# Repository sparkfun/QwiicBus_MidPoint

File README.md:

SparkFun QwiicBus MidPoint
========================================

[*SparkFun QwiicBus MidPoint (COM-18000)*](https://www.sparkfun.com/products/18000)

The SparkFun QwiicBus MidPoint works in tandem with the [SparkFun QwiicBus EndPoint](https://www.sparkfun.com/products/16988) to drop in I<sup>2</sup>C connections into a long-distance wired differential I<sup>2</sup>C bus. 
Featuring the PCA9615, the MidPoint translates a standard two-wire I<sup>2</sup>C signal to a 4-wire differential signal to allow long-distance and/or isolated wired buses. The board also includes a buck regulator that can be enabled to combat voltage drop over long distances as well as deliver more current to attached devices.

Repository Contents
-------------------

* **/Hardware** - Eagle design files (.brd, .sch)
* **/Production** - Production panel files (.brd)

Documentation
--------------
* **[Hookup Guide](https://learn.sparkfun.com/tutorials/sparkfun-qwiicbus-hookup-guide)** - Basic hookup guide for the SparkFun QwiicBus (MidPoint and EndPoint).

Product Versions
----------------
* [COM-18000](https://www.sparkfun.com/products/18000)- Initial QwiicBus MidPoint release
* [COM-16988](https://www.sparkfun.com/products/16988) - QwiicBus EndPoint initial release
* [KIT-17250](https://www.sparkfun.com/products/17250) - The SparkFun QwiicBus Kit includes 2 EndPoints, 1 MidPoint and a pair of Ethernet cables to get started with the QwiicBus.

License Information
-------------------

This product is _**open source**_! 

Please review the LICENSE.md file for license information. 

If you have any questions or concerns on licensing, please contact technical support on our [SparkFun forums](https://forum.sparkfun.com/viewforum.php?f=152).

Distributed as-is; no warranty is given.

- Your friends at SparkFun.

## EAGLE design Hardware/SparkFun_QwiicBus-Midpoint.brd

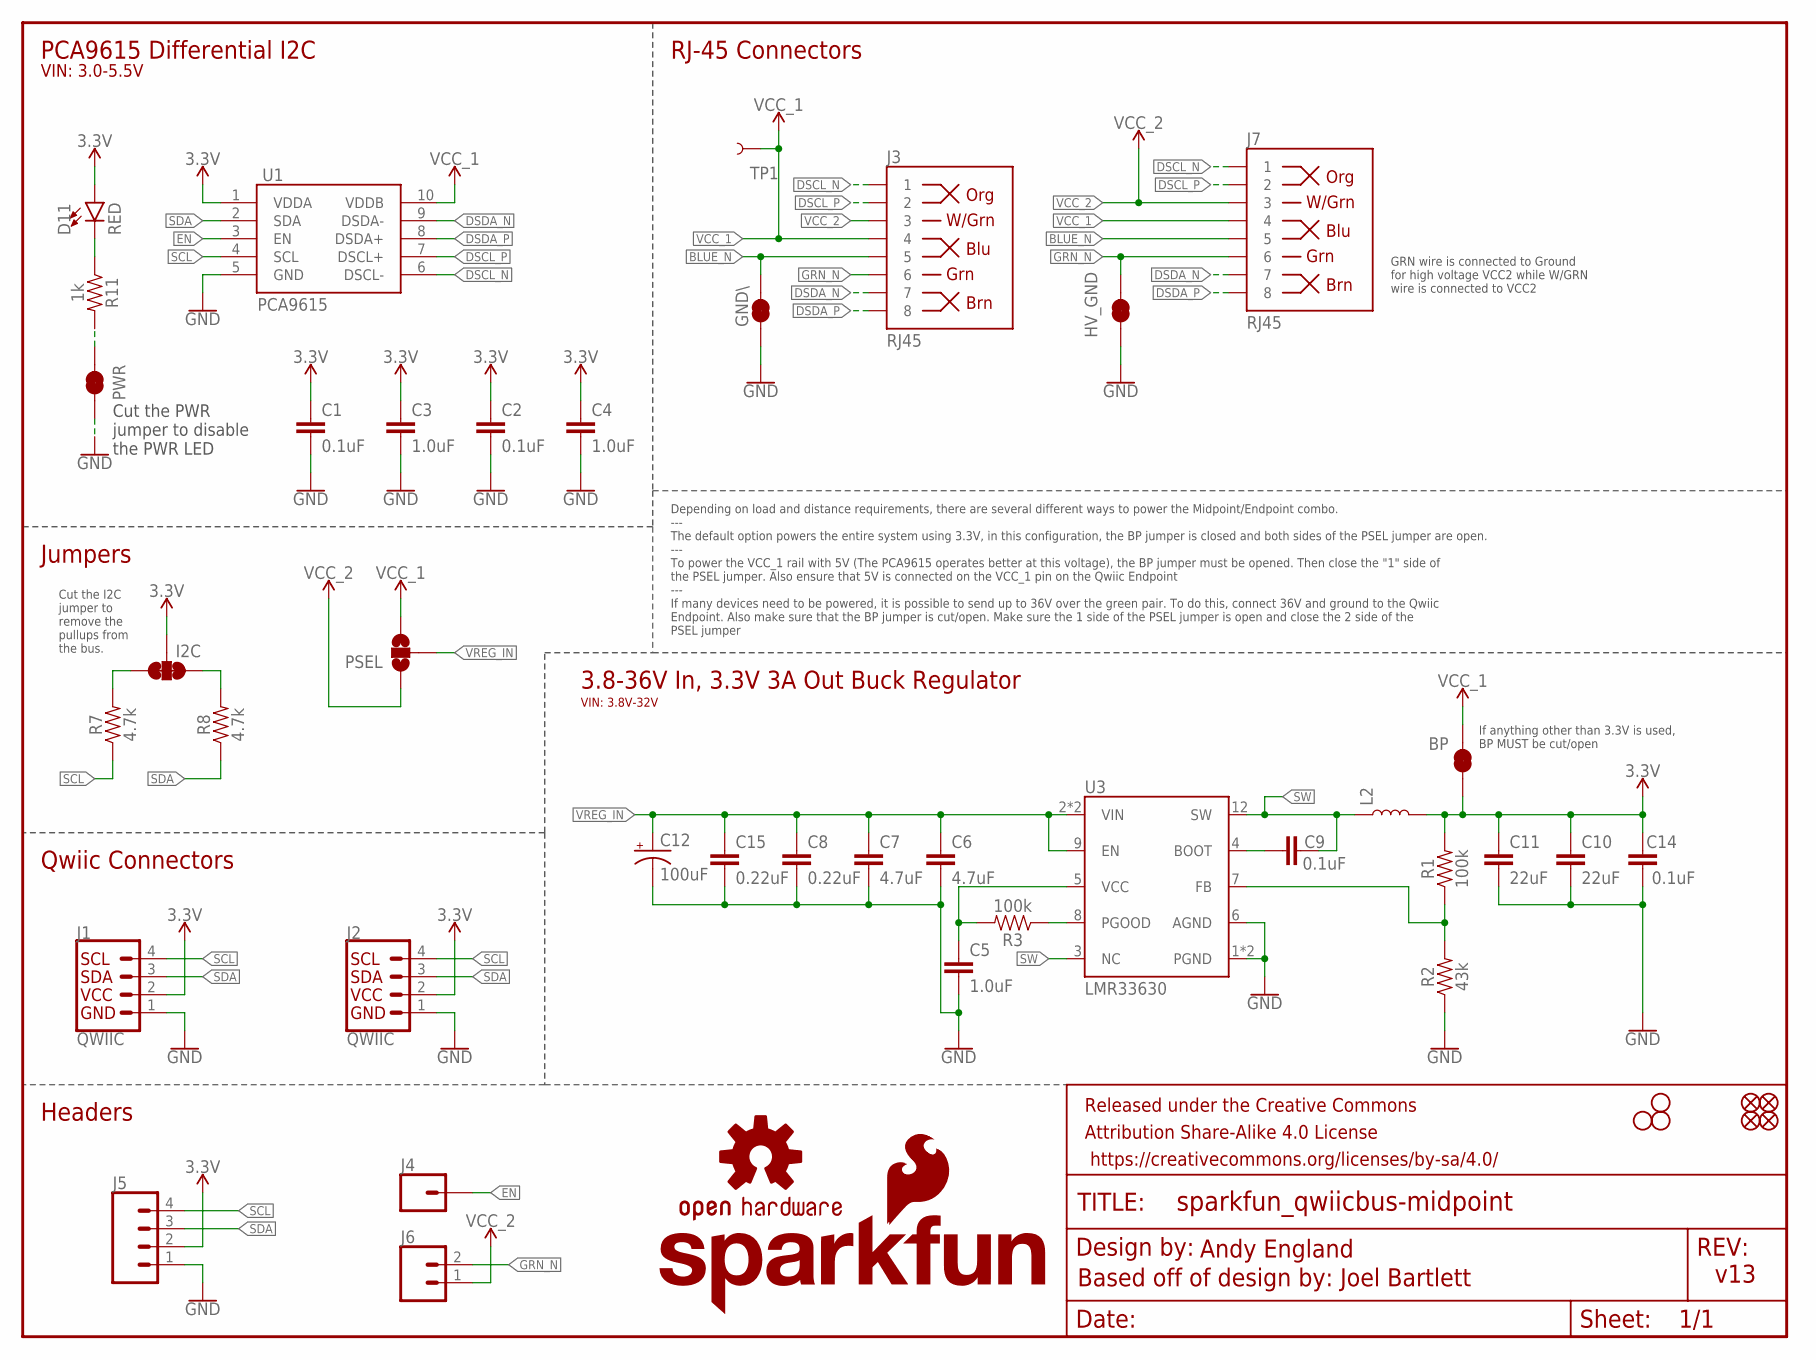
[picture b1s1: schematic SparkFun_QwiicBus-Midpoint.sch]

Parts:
BP: JUMPER-SMT_2_NC_TRACE_SILK; SMT-JUMPER_2_NC_TRACE_SILK
C1, C2, C9, C14: 0.1uF; 0603
C3, C4, C5: 1.0uF; 0603
C6, C7: 4.7uF; 0805
C8, C15: 0.22uF; 0603
C10, C11: 22uF; 1210
C12: 100uF; 8X10.5
D11: RED; LED-0603
FD1, FD2, FD3, FD4: FIDUCIALUFIDUCIAL; FIDUCIAL-MICRO
FRAME1: FRAME-LETTER; CREATIVE_COMMONS
GND\: JUMPER-SMT_2_NC_TRACE_SILK; SMT-JUMPER_2_NC_TRACE_SILK
H2, H3, H4: STAND-OFF
HV_GND: JUMPER-SMT_2_NC_TRACE_SILK; SMT-JUMPER_2_NC_TRACE_SILK
I2C: JUMPER-SMT_3_2-NC_TRACE_SILK; SMT-JUMPER_3_2-NC_TRACE_SILK
J1, J2: QWIIC; JST04_1MM_RA
J3, J7: RJ45; RJ45-8
J4: CONN_01PTH_NO_SILK_YES_STOP; 1X01_NO_SILK
J5: CONN_041X04_NO_SILK; 1X04_NO_SILK
J6: CONN_021X02_NO_SILK; 1X02_NO_SILK
L2: 2.2uH; INDUCTOR_5X5MM
LOGO1: OSHW-LOGOM; OSHW-LOGO-M
LOGO3: SFE_LOGO_FLAME.2_INCH; SFE_LOGO_FLAME_.2
LOGO4: SFE_LOGO_NAME_FLAME.1_INCH; SFE_LOGO_NAME_FLAME_.1
PSEL: JUMPER-SMT_3_NO_SILK; SMT-JUMPER_3_NO_SILK
PWR: JUMPER-SMT_2_NC_TRACE_SILK; SMT-JUMPER_2_NC_TRACE_SILK
R1, R3: 100k; 0603
R2: 43k; 0603
R7, R8: 4.7k; 0603
R11: 1k; 0603
TP1: TEST-POINT3; PAD.03X.03
U1: PCA9615; TSSOP10
U3: LMR33630; VQFN-HR-12

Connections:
3.3V: BP.1, C1.1, C2.1, C3.1, C4.1, C10.1, C11.1, C14.1, D11.A, I2C.2, J1.2, J2.2, J5.2, L2.P$2 (2), R1.2, U1.1 (VDDA)
BLUE_N: GND\.2, J3.5, J7.5
DSCL_N: J3.1, J7.1, U1.6 (DSCL-)
DSCL_P: J3.2, J7.2, U1.7 (DSCL+)
DSDA_N: J3.7, J7.7, U1.9 (DSDA-)
DSDA_P: J3.8, J7.8, U1.8 (DSDA+)
EN: J4.1, U1.3 (EN)
GND: C1.2, C2.2, C3.2, C4.2, C5.2, C6.2, C7.2, C8.2, C10.2, C11.2, C12.-, C14.2, C15.2, GND\.1, HV_GND.1, J1.1, J2.1, J5.1, PWR.1, R2.1, U1.5 (GND), U3.1 (PGND), U3.6 (AGND), U3.11 (PGND)
GRN_N: HV_GND.2, J3.6, J6.2, J7.6
unnamed: C9.1, U3.4 (BOOT)
unnamed: I2C.1, R8.2
unnamed: I2C.3, R7.2
unnamed: R1.1, R2.2, U3.7 (FB)
unnamed: R3.1, U3.8 (PGOOD)
unnamed: C5.1, R3.2, U3.5 (VCC)
unnamed: D11.C, R11.1
unnamed: PWR.2, R11.2
SCL: J1.4, J2.4, J5.4, R7.1, U1.4 (SCL)
SDA: J1.3, J2.3, J5.3, R8.1, U1.2 (SDA)
SW: C9.2, L2.P$1 (1), U3.3 (NC), U3.12 (SW)
VCC_1: BP.2, J3.4, J7.4, PSEL.3, TP1.P$1, U1.10 (VDDB)
VCC_2: J3.3, J6.1, J7.3, PSEL.1
VREG_IN: C6.1, C7.1, C8.1, C12.+, C15.1, PSEL.2, U3.2 (VIN), U3.9 (EN), U3.10 (VIN)

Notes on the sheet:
Andy England
PCA9615 Differential I2C
Qwiic Connectors
v13
Cut the I2C jumper to remove the pullups from the bus.
Headers
Jumpers
RJ-45 Connectors
Based off of design by: Joel Bartlett
Cut the PWR jumper to disable the PWR LED
3.8-36V In, 3.3V 3A Out Buck Regulator
VIN: 3.8V-32V
Depending on load and distance requirements, there are several different ways to power the Midpoint/Endpoint combo. --- The default option powers the entire system using 3.3V, in this configuration, the BP jumper is closed and both sides of the PSEL jumper are open. --- To power the VCC_1 rail with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
VIN: 3.0-5.5V
GRN wire is connected to Ground for high voltage VCC2 while W/GRN wire is connected to VCC2
If anything other than 3.3V is used, BP MUST be cut/open

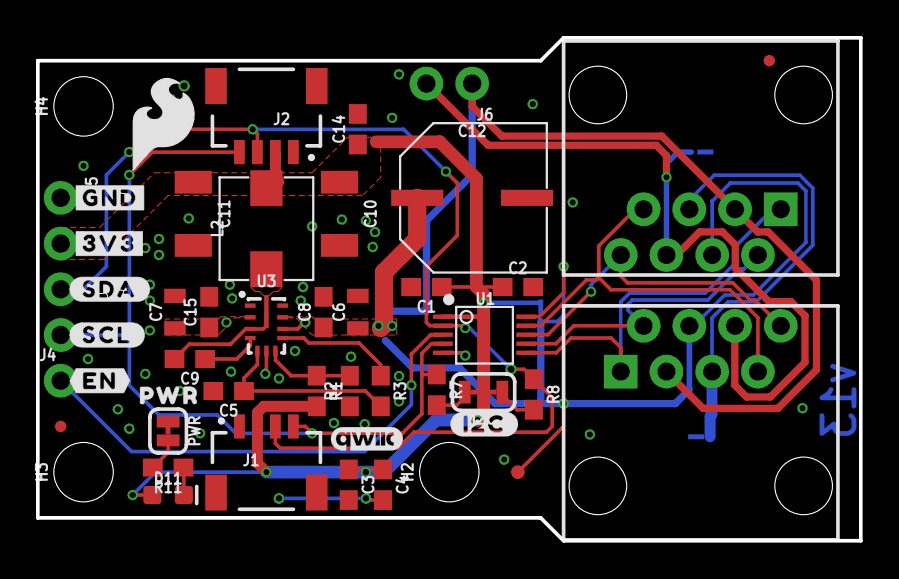
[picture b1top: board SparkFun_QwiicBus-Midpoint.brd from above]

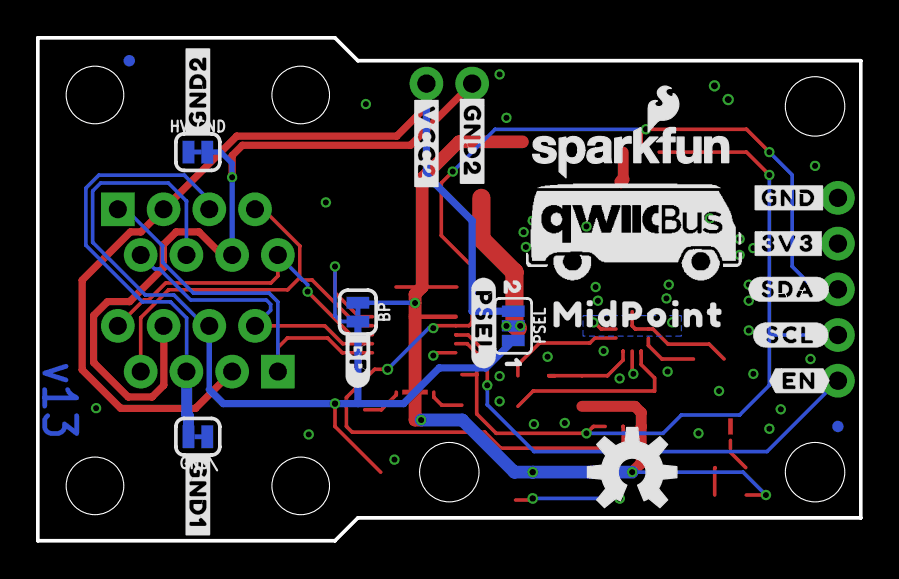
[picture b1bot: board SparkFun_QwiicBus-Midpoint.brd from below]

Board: 2 copper layers, 45.7 x 27.9 mm, 73 parts (23 on the bottom side), 23 nets.

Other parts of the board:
U$1, U$7: #GND#0
U$2, U$8: #3V3#0
U$3, U$9: #SDA#0
U$4, U$10: #SCL#0
U$5: #BP#0
U$6, U$12: #EN#0
U$11, U$24: #GND2#0
U$13: #I2C#0
U$14: #GND1#0
U$15: QWIICBUS#WORKING#LOGO#JPG
U$16: #VCC2#0
U$17: #PSEL#0
U$18: 10
U$19: 20
U$20: ORDERING_INSTRUCTIONS
U$22: QWIIC_4MM
U$23: PWR0
U$30: MIDPOINT0

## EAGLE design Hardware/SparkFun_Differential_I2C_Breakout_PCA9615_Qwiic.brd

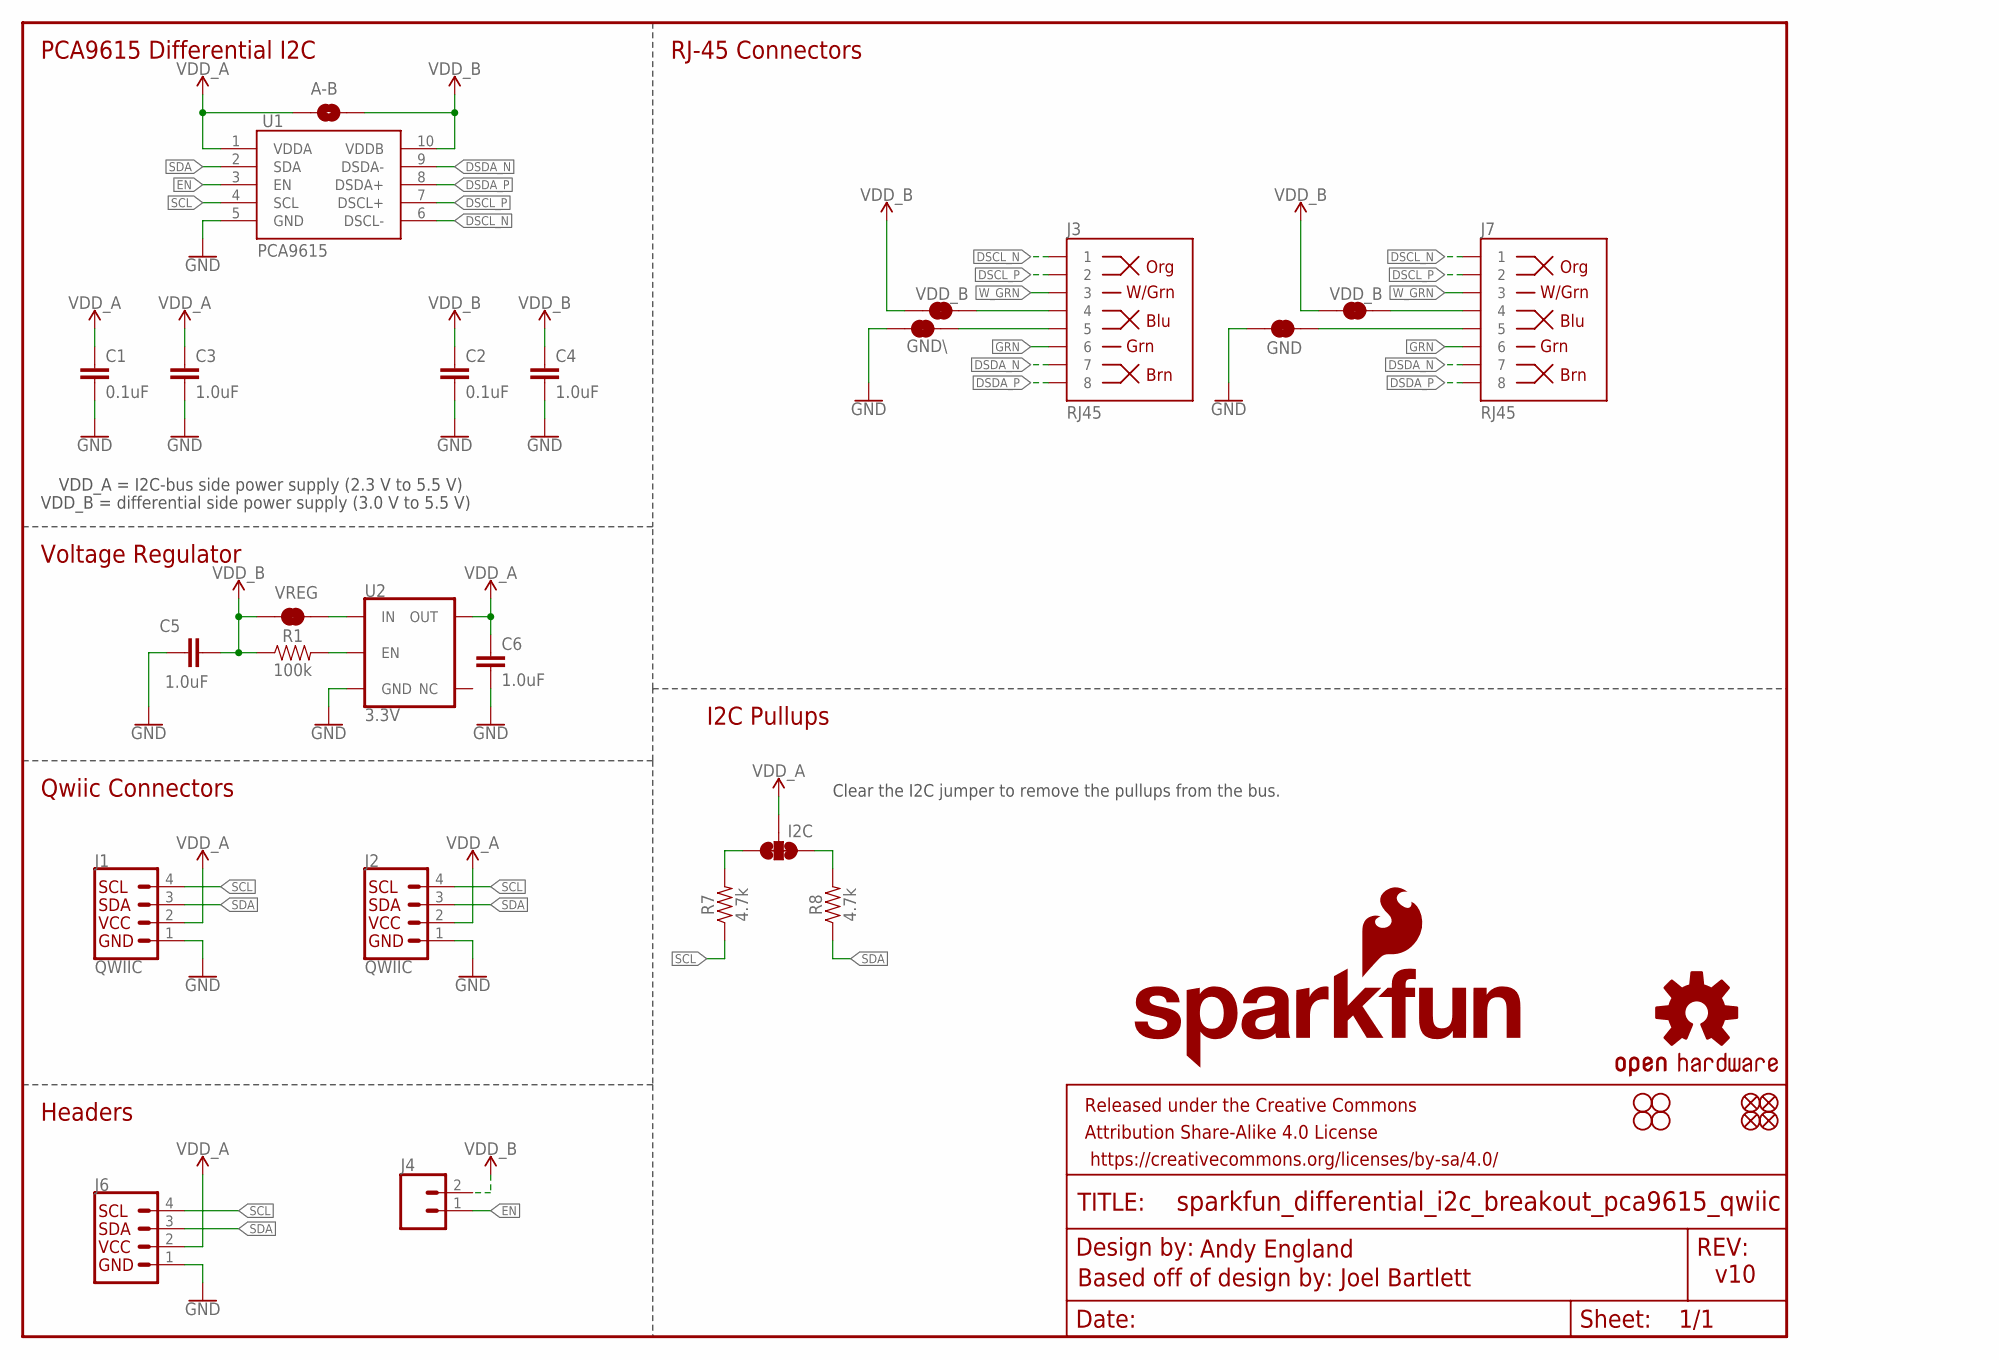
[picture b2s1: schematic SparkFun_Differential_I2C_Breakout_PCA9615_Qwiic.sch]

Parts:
A-B: JUMPER-SMT_2_NO_SILK; SMT-JUMPER_2_NO_SILK
C1, C2: 0.1uF; 0603
C3, C4, C5, C6: 1.0uF; 0603
FD1, FD2, FD3, FD4: FIDUCIALUFIDUCIAL; FIDUCIAL-MICRO
FRAME1: FRAME-LETTER; CREATIVE_COMMONS
GND\: JUMPER-SMT_2_NC_TRACE_SILK; SMT-JUMPER_2_NC_TRACE_SILK
H1, H2, H3, H4: STAND-OFF
I2C: JUMPER-SMT_3_2-NC_TRACE_SILK; SMT-JUMPER_3_2-NC_TRACE_SILK
J1, J2: QWIIC; JST04_1MM_RA
J3, J7: RJ45; RJ45-8
J4: CONN_021X02_NO_SILK; 1X02_NO_SILK
J6: I2C_STANDARD_NO_SILK; 1X04_NO_SILK
JP5, JP6: JUMPER-SMT_2_NC_TRACE_SILK; SMT-JUMPER_2_NC_TRACE_SILK
LOGO1: OSHW-LOGOM; OSHW-LOGO-M
LOGO5: SFE_LOGO_NAME_FLAME.1_INCH; SFE_LOGO_NAME_FLAME_.1
R1: 100k; 0603
R7, R8: 4.7k; 0603
U1: PCA9615; TSSOP10
U2: 3.3V; SOT23-5
VDD_B: JUMPER-SMT_2_NC_TRACE_SILK; SMT-JUMPER_2_NC_TRACE_SILK
VREG: JUMPER-SMT_2_NC_TRACE_SILK; SMT-JUMPER_2_NC_TRACE_SILK

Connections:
DSCL_N: J3.1, J7.1, U1.6 (DSCL-)
DSCL_P: J3.2, J7.2, U1.7 (DSCL+)
DSDA_N: J3.7, J7.7, U1.9 (DSDA-)
DSDA_P: J3.8, J7.8, U1.8 (DSDA+)
EN: J4.1, U1.3 (EN)
GND: C1.2, C2.2, C3.2, C4.2, C5.1, C6.2, GND\.1, J1.1, J2.1, J6.1 (GND), JP6.1, U1.5 (GND), U2.2 (GND)
GRN: J3.6, J7.6
unnamed: J3.4, VDD_B.2
unnamed: GND\.2, J3.5
unnamed: I2C.1, R8.2
unnamed: I2C.3, R7.2
unnamed: J7.4, JP5.2
unnamed: J7.5, JP6.2
unnamed: R1.2, U2.3 (EN)
unnamed: U2.1 (IN), VREG.2
SCL: J1.4, J2.4, J6.4 (SCL), R7.1, U1.4 (SCL)
SDA: J1.3, J2.3, J6.3 (SDA), R8.1, U1.2 (SDA)
VDD_A: A-B.1, C1.1, C3.1, C6.1, I2C.2, J1.2, J2.2, J6.2 (VCC), U1.1 (VDDA), U2.5 (OUT)
VDD_B: A-B.2, C2.1, C4.1, C5.2, J4.2, JP5.1, R1.1, U1.10 (VDDB), VDD_B.1, VREG.1
W_GRN: J3.3, J7.3

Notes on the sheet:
Andy England
PCA9615 Differential I2C
Qwiic Connectors
v10
Clear the I2C jumper to remove the pullups from the bus.
Headers
I2C Pullups
RJ-45 Connectors
VDD_A = I2C-bus side power supply (2.3 V to 5.5 V)
VDD_B = differential side power supply (3.0 V to 5.5 V)
Voltage Regulator
VDD_B
GND
Based off of design by: Joel Bartlett

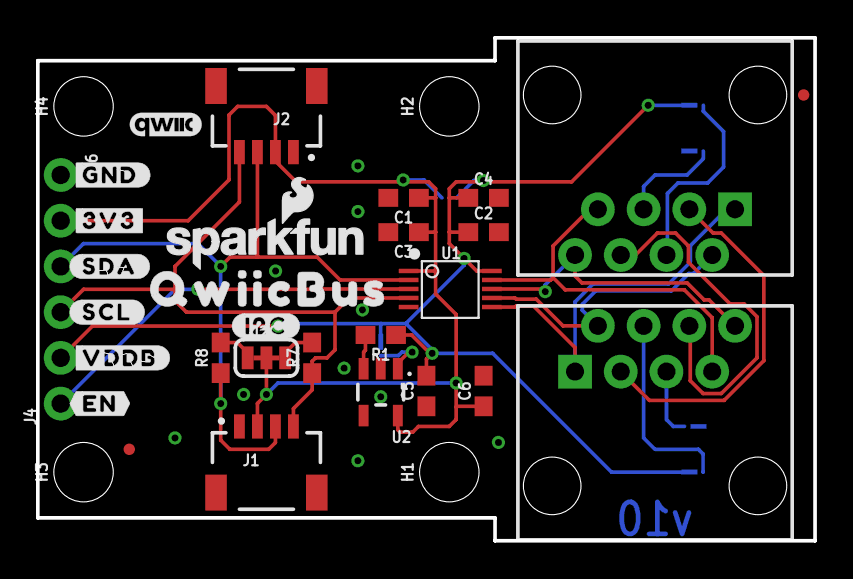
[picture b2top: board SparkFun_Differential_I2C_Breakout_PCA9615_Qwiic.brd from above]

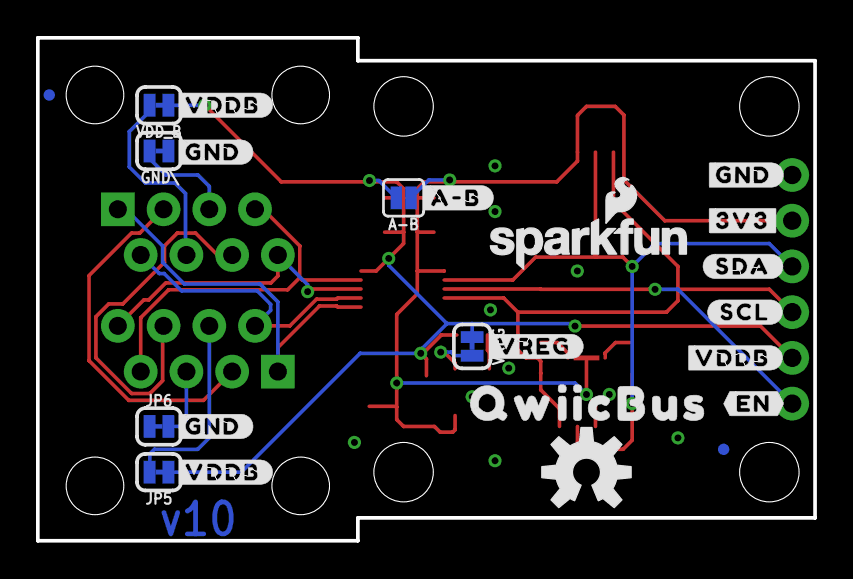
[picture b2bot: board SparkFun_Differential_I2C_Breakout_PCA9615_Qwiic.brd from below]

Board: 2 copper layers, 43.2 x 27.9 mm, 58 parts (23 on the bottom side), 20 nets.

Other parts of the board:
LOGO2: SFE_LOGO_NAME_FLAME.1_INCH; SFE_LOGO_NAME_FLAME_.1
U$1, U$7, U$20, U$21: #GND#0
U$2, U$8: #3V3#0
U$3, U$9: #SDA#0
U$4, U$10: #SCL#0
U$5, U$16, U$18, U$19: #VDDB#0
U$6, U$12: #EN#0
U$11: #A#B#0
U$13: #I2C#0
U$14, U$15: QWIICBUS0
U$17: #VREG#0
U$22: QWIIC_4MM

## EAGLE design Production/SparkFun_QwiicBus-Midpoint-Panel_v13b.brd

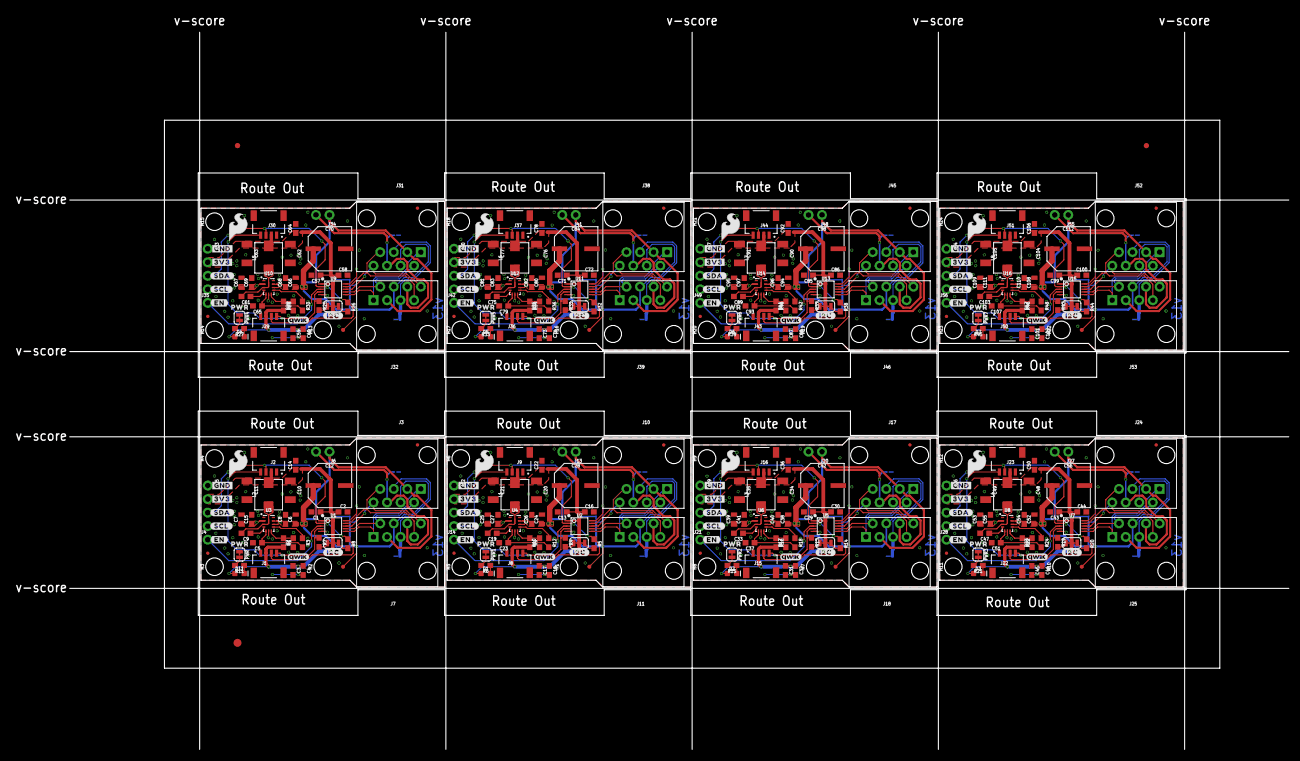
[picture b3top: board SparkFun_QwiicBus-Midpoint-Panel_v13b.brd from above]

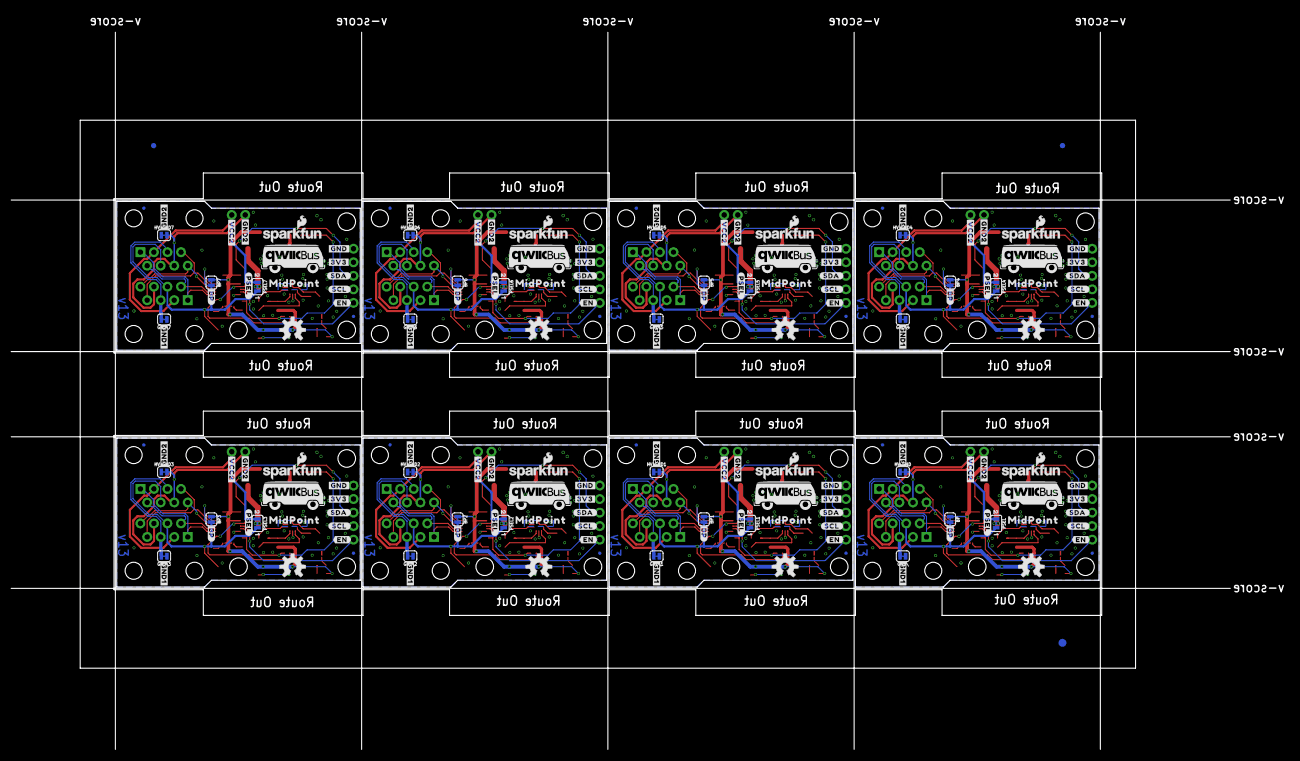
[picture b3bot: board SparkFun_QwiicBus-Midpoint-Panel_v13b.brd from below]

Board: 2 copper layers, 239.8 x 138.6 mm, 574 parts (187 on the bottom side), 184 nets.

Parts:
BP, BP1, BP2, BP3, BP4, BP5, BP6, BP7: JUMPER-SMT_2_NC_TRACE_SILK; SMT-JUMPER_2_NC_TRACE_SILK
C1, C2, C9, C13, C14, C16, C19, C22, C29, C30, C33, C36, C43, C44, C47, C50, C57, C58, C61, C64, C71, C72, C75, C78, C85, C86, C89, C92, C99, C100, C103, C106: 0.1uF; 0603
C3, C4, C5, C17, C18, C23, C31, C32, C37, C45, C46, C51, C59, C60, C65, C73, C74, C79, C87, C88, C93, C101, C102, C107: 1.0uF; 0603
C6, C7, C24, C25, C38, C39, C52, C53, C66, C67, C80, C81, C94, C95, C108, C109: 4.7uF; 0805
C8, C15, C26, C27, C40, C41, C54, C55, C68, C69, C82, C83, C96, C97, C110, C111: 0.22uF; 0603
C10, C11, C20, C21, C34, C35, C48, C49, C62, C63, C76, C77, C90, C91, C104, C105: 22uF; 1210
C12, C28, C42, C56, C70, C84, C98, C112: 100uF; 8X10.5
D1, D2, D3, D4, D5, D6, D7, D11: RED; LED-0603
E$1, E$2, E$3, E$4: FIDUCIAL-1X2
E$5, E$6: FIDUCIAL-1.5X3
FD1, FD2, FD3, FD4, FD5, FD6, FD7, FD8, FD9, FD10, FD11, FD12, FD13, FD14, FD15, FD16, FD17, FD18, FD19, FD20, FD21, FD22, FD23, FD24, FD25, FD26, FD27, FD28, FD29, FD30, FD31, FD32: FIDUCIALUFIDUCIAL; FIDUCIAL-MICRO
GND\, GND\1, GND\2, GND\3, GND\4, GND\5, GND\6, GND\7: JUMPER-SMT_2_NC_TRACE_SILK; SMT-JUMPER_2_NC_TRACE_SILK
H1, H2, H3, H4, H5, H6, H7, H8, H9, H10, H11, H12, H13, H14, H15, H16, H17, H18, H19, H20, H21, H22, H23, H24: STAND-OFF
HV_GND, HV_GND1, HV_GND2, HV_GND3, HV_GND4, HV_GND5, HV_GND6, HV_GND7: JUMPER-SMT_2_NC_TRACE_SILK; SMT-JUMPER_2_NC_TRACE_SILK
I2C, I2C1, I2C2, I2C3, I2C4, I2C5, I2C6, I2C7: JUMPER-SMT_3_2-NC_TRACE_SILK; SMT-JUMPER_3_2-NC_TRACE_SILK
J1, J2, J8, J9, J15, J16, J22, J23, J29, J30, J36, J37, J43, J44, J50, J51: QWIIC; JST04_1MM_RA
J3, J7, J10, J11, J17, J18, J24, J25, J31, J32, J38, J39, J45, J46, J52, J53: RJ45; RJ45-8
J4, J14, J21, J28, J35, J42, J49, J56: 1X01_NO_SILK
J5, J12, J19, J26, J33, J40, J47, J54: 1X04_NO_SILK
J6, J13, J20, J27, J34, J41, J48, J55: 1X02_NO_SILK
L1, L2, L3, L4, L5, L6, L7, L8: 2.2uH; INDUCTOR_5X5MM
LOGO1, LOGO2, LOGO7, LOGO10, LOGO13, LOGO16, LOGO19, LOGO22: OSHW-LOGOM; OSHW-LOGO-M
LOGO3, LOGO5, LOGO8, LOGO11, LOGO14, LOGO17, LOGO20, LOGO23: SFE_LOGO_FLAME.2_INCH; SFE_LOGO_FLAME_.2
LOGO4, LOGO6, LOGO9, LOGO12, LOGO15, LOGO18, LOGO21, LOGO24: SFE_LOGO_NAME_FLAME.1_INCH; SFE_LOGO_NAME_FLAME_.1
PSEL, PSEL1, PSEL2, PSEL3, PSEL4, PSEL5, PSEL6, PSEL7: JUMPER-SMT_3_NO_SILK; SMT-JUMPER_3_NO_SILK
PWR, PWR1, PWR2, PWR3, PWR4, PWR5, PWR6, PWR7: JUMPER-SMT_2_NC_TRACE_SILK; SMT-JUMPER_2_NC_TRACE_SILK
R1, R3, R9, R12, R16, R18, R22, R24, R28, R30, R34, R36, R40, R42, R46, R48: 100k; 0603
R2, R10, R17, R23, R29, R35, R41, R47: 43k; 0603
R4, R5, R7, R8, R13, R14, R19, R20, R25, R26, R31, R32, R37, R38, R43, R44: 4.7k; 0603
R6, R11, R15, R21, R27, R33, R39, R45: 1k; 0603
TP1, TP2, TP3, TP4, TP5, TP6, TP7, TP8: TEST-POINT3; PAD.03X.03
U1, U2, U5, U7, U9, U11, U13, U15: PCA9615; TSSOP10
U3, U4, U6, U8, U10, U12, U14, U16: LMR33630; VQFN-HR-12
U$1, U$7, U$20, U$28, U$47, U$52, U$70, U$75, U$93, U$98, U$116, U$121, U$139, U$144, U$162, U$167: #GND#0
U$2, U$8, U$21, U$29, U$48, U$53, U$71, U$76, U$94, U$99, U$117, U$122, U$140, U$145, U$163, U$168: #3V3#0
U$3, U$9, U$25, U$31, U$49, U$54, U$72, U$77, U$95, U$100, U$118, U$123, U$141, U$146, U$164, U$169: #SDA#0
U$4, U$10, U$26, U$32, U$50, U$55, U$73, U$78, U$96, U$101, U$119, U$124, U$142, U$147, U$165, U$170: #SCL#0
U$5, U$46, U$69, U$92, U$115, U$138, U$161, U$184: #BP#0
U$6, U$12, U$27, U$33, U$51, U$56, U$74, U$79, U$97, U$102, U$120, U$125, U$143, U$148, U$166, U$171: #EN#0
U$11, U$24, U$40, U$44, U$63, U$67, U$86, U$90, U$109, U$113, U$132, U$136, U$155, U$159, U$178, U$182: #GND2#0
U$13, U$38, U$61, U$84, U$107, U$130, U$153, U$176: #I2C#0
U$14, U$45, U$68, U$91, U$114, U$137, U$160, U$183: #GND1#0
U$15, U$37, U$60, U$83, U$106, U$129, U$152, U$175: QWIICBUS#WORKING#LOGO#JPG
U$16, U$39, U$62, U$85, U$108, U$131, U$154, U$177: #VCC2#0
U$17, U$41, U$64, U$87, U$110, U$133, U$156, U$179: #PSEL#0
U$18, U$42, U$65, U$88, U$111, U$134, U$157, U$180: 10
U$19, U$43, U$66, U$89, U$112, U$135, U$158, U$181: 20
U$22, U$34, U$57, U$80, U$103, U$126, U$149, U$172: QWIIC_4MM
U$23, U$35, U$58, U$81, U$104, U$127, U$150, U$173: PWR0
U$30, U$36, U$59, U$82, U$105, U$128, U$151, U$174: MIDPOINT0

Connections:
3.3V: BP.1, C1.1, C2.1, C3.1, C4.1, C10.1, C11.1, C14.1, D11.A, I2C.2, J1.2, J2.2, J5.2, L2.P$2, R1.2, U1.1
3.3V1: BP1.1, C13.1, C16.1, C17.1, C18.1, C20.1, C21.1, C22.1, D1.A, I2C1.2, J8.2, J9.2, J12.2, L1.P$2, R9.2, U2.1
3.3V2: BP2.1, C29.1, C30.1, C31.1, C32.1, C34.1, C35.1, C36.1, D2.A, I2C2.2, J15.2, J16.2, J19.2, L3.P$2, R16.2, U5.1
3.3V3: BP3.1, C43.1, C44.1, C45.1, C46.1, C48.1, C49.1, C50.1, D3.A, I2C3.2, J22.2, J23.2, J26.2, L4.P$2, R22.2, U7.1
3.3V4: BP4.1, C57.1, C58.1, C59.1, C60.1, C62.1, C63.1, C64.1, D4.A, I2C4.2, J29.2, J30.2, J33.2, L5.P$2, R28.2, U9.1
3.3V5: BP5.1, C71.1, C72.1, C73.1, C74.1, C76.1, C77.1, C78.1, D5.A, I2C5.2, J36.2, J37.2, J40.2, L6.P$2, R34.2, U11.1
3.3V6: BP6.1, C85.1, C86.1, C87.1, C88.1, C90.1, C91.1, C92.1, D6.A, I2C6.2, J43.2, J44.2, J47.2, L7.P$2, R40.2, U13.1
3.3V7: BP7.1, C99.1, C100.1, C101.1, C102.1, C104.1, C105.1, C106.1, D7.A, I2C7.2, J50.2, J51.2, J54.2, L8.P$2, R46.2, U15.1
BLUE_N: GND\.2, J3.5, J7.5
BLUE_N1: GND\1.2, J10.5, J11.5
BLUE_N2: GND\2.2, J17.5, J18.5
BLUE_N3: GND\3.2, J24.5, J25.5
BLUE_N4: GND\4.2, J31.5, J32.5
BLUE_N5: GND\5.2, J38.5, J39.5
BLUE_N6: GND\6.2, J45.5, J46.5
BLUE_N7: GND\7.2, J52.5, J53.5
DSCL_N: J3.1, J7.1, U1.6
DSCL_N1: J10.1, J11.1, U2.6
DSCL_N2: J17.1, J18.1, U5.6
DSCL_N3: J24.1, J25.1, U7.6
DSCL_N4: J31.1, J32.1, U9.6
DSCL_N5: J38.1, J39.1, U11.6
DSCL_N6: J45.1, J46.1, U13.6
DSCL_N7: J52.1, J53.1, U15.6
DSCL_P: J3.2, J7.2, U1.7
DSCL_P1: J10.2, J11.2, U2.7
DSCL_P2: J17.2, J18.2, U5.7
DSCL_P3: J24.2, J25.2, U7.7
DSCL_P4: J31.2, J32.2, U9.7
DSCL_P5: J38.2, J39.2, U11.7
DSCL_P6: J45.2, J46.2, U13.7
DSCL_P7: J52.2, J53.2, U15.7
DSDA_N: J3.7, J7.7, U1.9
DSDA_N1: J10.7, J11.7, U2.9
DSDA_N2: J17.7, J18.7, U5.9
DSDA_N3: J24.7, J25.7, U7.9
DSDA_N4: J31.7, J32.7, U9.9
DSDA_N5: J38.7, J39.7, U11.9
DSDA_N6: J45.7, J46.7, U13.9
DSDA_N7: J52.7, J53.7, U15.9
DSDA_P: J3.8, J7.8, U1.8
DSDA_P1: J10.8, J11.8, U2.8
DSDA_P2: J17.8, J18.8, U5.8
DSDA_P3: J24.8, J25.8, U7.8
DSDA_P4: J31.8, J32.8, U9.8
DSDA_P5: J38.8, J39.8, U11.8
DSDA_P6: J45.8, J46.8, U13.8
DSDA_P7: J52.8, J53.8, U15.8
EN: J4.1, U1.3
EN1: J14.1, U2.3
EN2: J21.1, U5.3
EN3: J28.1, U7.3
EN4: J35.1, U9.3
EN5: J42.1, U11.3
EN6: J49.1, U13.3
EN7: J56.1, U15.3
GND: C1.2, C2.2, C3.2, C4.2, C5.2, C6.2, C7.2, C8.2, C10.2, C11.2, C12.-, C14.2, C15.2, GND\.1, HV_GND.1, J1.1, J2.1, J5.1, PWR.1, R2.1, U1.5, U3.1, U3.6, U3.11
GND1: C13.2, C16.2, C17.2, C18.2, C20.2, C21.2, C22.2, C23.2, C24.2, C25.2, C26.2, C27.2, C28.-, GND\1.1, HV_GND1.1, J8.1, J9.1, J12.1, PWR1.1, R10.1, U2.5, U4.1, U4.6, U4.11
GND2: C29.2, C30.2, C31.2, C32.2, C34.2, C35.2, C36.2, C37.2, C38.2, C39.2, C40.2, C41.2, C42.-, GND\2.1, HV_GND2.1, J15.1, J16.1, J19.1, PWR2.1, R17.1, U5.5, U6.1, U6.6, U6.11
GND3: C43.2, C44.2, C45.2, C46.2, C48.2, C49.2, C50.2, C51.2, C52.2, C53.2, C54.2, C55.2, C56.-, GND\3.1, HV_GND3.1, J22.1, J23.1, J26.1, PWR3.1, R23.1, U7.5, U8.1, U8.6, U8.11
GND4: C57.2, C58.2, C59.2, C60.2, C62.2, C63.2, C64.2, C65.2, C66.2, C67.2, C68.2, C69.2, C70.-, GND\4.1, HV_GND4.1, J29.1, J30.1, J33.1, PWR4.1, R29.1, U9.5, U10.1, U10.6, U10.11
GND5: C71.2, C72.2, C73.2, C74.2, C76.2, C77.2, C78.2, C79.2, C80.2, C81.2, C82.2, C83.2, C84.-, GND\5.1, HV_GND5.1, J36.1, J37.1, J40.1, PWR5.1, R35.1, U11.5, U12.1, U12.6, U12.11
GND6: C85.2, C86.2, C87.2, C88.2, C90.2, C91.2, C92.2, C93.2, C94.2, C95.2, C96.2, C97.2, C98.-, GND\6.1, HV_GND6.1, J43.1, J44.1, J47.1, PWR6.1, R41.1, U13.5, U14.1, U14.6, U14.11
GND7: C99.2, C100.2, C101.2, C102.2, C104.2, C105.2, C106.2, C107.2, C108.2, C109.2, C110.2, C111.2, C112.-, GND\7.1, HV_GND7.1, J50.1, J51.1, J54.1, PWR7.1, R47.1, U15.5, U16.1, U16.6, U16.11
GRN_N: HV_GND.2, J3.6, J6.2, J7.6
GRN_N1: HV_GND1.2, J10.6, J11.6, J13.2
GRN_N2: HV_GND2.2, J17.6, J18.6, J20.2
GRN_N3: HV_GND3.2, J24.6, J25.6, J27.2
GRN_N4: HV_GND4.2, J31.6, J32.6, J34.2
GRN_N5: HV_GND5.2, J38.6, J39.6, J41.2
GRN_N6: HV_GND6.2, J45.6, J46.6, J48.2
GRN_N7: HV_GND7.2, J52.6, J53.6, J55.2
unnamed: C9.1, U3.4
unnamed: I2C1.1, R5.2
unnamed: I2C.1, R8.2
unnamed: I2C.3, R7.2
unnamed: I2C1.3, R4.2
unnamed: R1.1, R2.2, U3.7
unnamed: R3.1, U3.8
unnamed: D1.C, R6.1
unnamed: C5.1, R3.2, U3.5
unnamed: PWR1.2, R6.2
unnamed: C19.1, U4.4
unnamed: R9.1, R10.2, U4.7
unnamed: D11.C, R11.1
unnamed: PWR.2, R11.2
unnamed: R12.1, U4.8
unnamed: C23.1, R12.2, U4.5
unnamed: I2C2.1, R14.2
unnamed: I2C2.3, R13.2
unnamed: D2.C, R15.1
unnamed: PWR2.2, R15.2
unnamed: C33.1, U6.4
unnamed: R16.1, R17.2, U6.7
unnamed: R18.1, U6.8
unnamed: C37.1, R18.2, U6.5
unnamed: I2C3.1, R20.2
unnamed: I2C3.3, R19.2
unnamed: D3.C, R21.1
unnamed: PWR3.2, R21.2
unnamed: C47.1, U8.4
unnamed: R22.1, R23.2, U8.7
unnamed: R24.1, U8.8
unnamed: C51.1, R24.2, U8.5
unnamed: I2C4.1, R26.2
unnamed: I2C4.3, R25.2
unnamed: D4.C, R27.1
unnamed: PWR4.2, R27.2
unnamed: C61.1, U10.4
unnamed: R28.1, R29.2, U10.7
unnamed: R30.1, U10.8
unnamed: C65.1, R30.2, U10.5
unnamed: I2C5.1, R32.2
unnamed: I2C5.3, R31.2
unnamed: D5.C, R33.1
unnamed: PWR5.2, R33.2
unnamed: C75.1, U12.4
unnamed: R34.1, R35.2, U12.7
unnamed: R36.1, U12.8
unnamed: C79.1, R36.2, U12.5
unnamed: I2C6.1, R38.2
unnamed: I2C6.3, R37.2
unnamed: D6.C, R39.1
unnamed: PWR6.2, R39.2
unnamed: C89.1, U14.4
unnamed: R40.1, R41.2, U14.7
unnamed: R42.1, U14.8
unnamed: C93.1, R42.2, U14.5
unnamed: I2C7.1, R44.2
unnamed: I2C7.3, R43.2
unnamed: D7.C, R45.1
unnamed: PWR7.2, R45.2
unnamed: C103.1, U16.4
unnamed: R46.1, R47.2, U16.7
unnamed: R48.1, U16.8
unnamed: C107.1, R48.2, U16.5
SCL: J1.4, J2.4, J5.4, R7.1, U1.4
SCL1: J8.4, J9.4, J12.4, R4.1, U2.4
SCL2: J15.4, J16.4, J19.4, R13.1, U5.4
SCL3: J22.4, J23.4, J26.4, R19.1, U7.4
SCL4: J29.4, J30.4, J33.4, R25.1, U9.4
SCL5: J36.4, J37.4, J40.4, R31.1, U11.4
SCL6: J43.4, J44.4, J47.4, R37.1, U13.4
SCL7: J50.4, J51.4, J54.4, R43.1, U15.4
SDA: J1.3, J2.3, J5.3, R8.1, U1.2
SDA1: J8.3, J9.3, J12.3, R5.1, U2.2
SDA2: J15.3, J16.3, J19.3, R14.1, U5.2
SDA3: J22.3, J23.3, J26.3, R20.1, U7.2
SDA4: J29.3, J30.3, J33.3, R26.1, U9.2
SDA5: J36.3, J37.3, J40.3, R32.1, U11.2
SDA6: J43.3, J44.3, J47.3, R38.1, U13.2
SDA7: J50.3, J51.3, J54.3, R44.1, U15.2
SW: C9.2, L2.P$1, U3.3, U3.12
SW1: C19.2, L1.P$1, U4.3, U4.12
SW2: C33.2, L3.P$1, U6.3, U6.12
SW3: C47.2, L4.P$1, U8.3, U8.12
SW4: C61.2, L5.P$1, U10.3, U10.12
SW5: C75.2, L6.P$1, U12.3, U12.12
SW6: C89.2, L7.P$1, U14.3, U14.12
SW7: C103.2, L8.P$1, U16.3, U16.12
VCC_1: BP.2, J3.4, J7.4, PSEL.3, TP1.P$1, U1.10
VCC_2: J3.3, J6.1, J7.3, PSEL.1
VCC_3: BP1.2, J10.4, J11.4, PSEL1.3, TP2.P$1, U2.10
VCC_4: J10.3, J11.3, J13.1, PSEL1.1
VCC_5: BP2.2, J17.4, J18.4, PSEL2.3, TP3.P$1, U5.10
VCC_6: J17.3, J18.3, J20.1, PSEL2.1
VCC_7: BP3.2, J24.4, J25.4, PSEL3.3, TP4.P$1, U7.10
VCC_8: J24.3, J25.3, J27.1, PSEL3.1
VCC_9: BP4.2, J31.4, J32.4, PSEL4.3, TP5.P$1, U9.10
VCC_10: J31.3, J32.3, J34.1, PSEL4.1
VCC_11: BP5.2, J38.4, J39.4, PSEL5.3, TP6.P$1, U11.10
VCC_12: J38.3, J39.3, J41.1, PSEL5.1
VCC_13: BP6.2, J45.4, J46.4, PSEL6.3, TP7.P$1, U13.10
VCC_14: J45.3, J46.3, J48.1, PSEL6.1
VCC_15: BP7.2, J52.4, J53.4, PSEL7.3, TP8.P$1, U15.10
VCC_16: J52.3, J53.3, J55.1, PSEL7.1
VREG_IN: C6.1, C7.1, C8.1, C12.+, C15.1, PSEL.2, U3.2, U3.9, U3.10
VREG_IN1: C24.1, C25.1, C26.1, C27.1, C28.+, PSEL1.2, U4.2, U4.9, U4.10
VREG_IN2: C38.1, C39.1, C40.1, C41.1, C42.+, PSEL2.2, U6.2, U6.9, U6.10
VREG_IN3: C52.1, C53.1, C54.1, C55.1, C56.+, PSEL3.2, U8.2, U8.9, U8.10
VREG_IN4: C66.1, C67.1, C68.1, C69.1, C70.+, PSEL4.2, U10.2, U10.9, U10.10
VREG_IN5: C80.1, C81.1, C82.1, C83.1, C84.+, PSEL5.2, U12.2, U12.9, U12.10
VREG_IN6: C94.1, C95.1, C96.1, C97.1, C98.+, PSEL6.2, U14.2, U14.9, U14.10
VREG_IN7: C108.1, C109.1, C110.1, C111.1, C112.+, PSEL7.2, U16.2, U16.9, U16.10

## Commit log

2020-07-02 updating net name to fix VDD_A issue
2020-07-06 post design review checklist changes
2020-07-06 saving all changes
2020-07-06 Post checklist double check
2020-07-28 adding grn pair
2020-07-30 adding qwiicBus silk
2020-07-31 pushing mid checklist changes
2020-08-05 Thickening VDDB
2020-08-18 adding buck regulator
2020-08-18 Sprinkling in some vias
2020-08-19 post review changes
2020-08-25 ordering protos
2020-10-19 post FarmHand Review
2020-10-20 post checklist changes
2020-12-07 starting hot swap work
2020-12-09 updating hotswap lib with new FET
2020-12-14 initial layout of hot swap controller
2020-12-14 finish routing
2020-12-15 pushing unsaved silk changes
2020-12-16 post-checklist changes
2020-12-16 pushing unsaved changes from double check
2021-02-10 rolling back to non hot swap version
2021-03-26 Create README.md
    Initial commit of README
2021-03-29 removing backup files adding gitignore
2021-04-02 RE-panelization for stronger inner-support tabs

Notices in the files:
parts and their libraries:
SparkFun-Aesthetics: Licensing: CC v3.0 Share-Alike You are welcome to use this library for commercial purposes.
SparkFun-Aesthetics: Released under the Creative Commons Attribution Share-Alike 4.0 License
SparkFun-Aesthetics: https://creativecommons.org/licenses/by-sa/4.0
